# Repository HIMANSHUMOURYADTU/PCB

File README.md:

# 🔌 Transformerless Power Supply PCB (2-Layer Design)

A compact, cost-effective **transformerless AC-DC power supply** PCB, designed on a **2-layer board**, ideal for low-power embedded systems or IoT applications. This design eliminates bulky transformers using capacitive dropper topology.

---

## ⚙️ Features

- 🧩 **Transformerless AC to DC Conversion**
- 🌐 **Input Voltage**: 230V AC (mains)
- ⚡ **Output Voltage**: 12V DC (based on design)
- 🔄 **Capacitive Dropper Circuit**
- 🧯 Overvoltage and short-circuit protection
- 🖨️ **2-Layer PCB** for easy fabrication
- 🔬 Designed using **KiCad** / *(change if EasyEDA, etc.)*

---

## 📁 Project Files

| File/Folder        | Description                                  |
|--------------------|----------------------------------------------|
| `*.powerwithouttrans.kicad_prl`      | KiCad project file                           |
| `*.powerwithouttrans_pcb`            | PCB layout                                   |
| `*.kicad_sch`                        | Circuit schematic                            |
| `images/`                            | PCB renders and layout screenshots           |
| `README.md`                          | This documentation                           |
| `LICENSE`                            | Open source license (e.g., MIT or CERN-OHL)  |

---

## 🧠 Circuit Description

This power supply utilizes an **X-rated safety capacitor** to drop mains AC voltage, followed by:
- **Bridge rectifier** for AC to DC conversion
- **Zener diode** or **regulator IC** for voltage stabilization
- **Snubber network & fuse** for protection

⚠️ **Caution**: This is a **non-isolated** design and must be used with care. Do not touch the circuit while it's powered. Suitable for **low-current, enclosed applications only**.

---

## 🖼️ PCB Layout & 3D View

| Top View | Bottom View |
|----------|-------------|
|  |  |

---

---

## 📝 License

This project is licensed under the **MIT License**. See the `LICENSE` file for more information.

---

## 🤝 Contributing

Contributions are welcome! Feel free to fork this repository, make enhancements, and submit a pull request.

---

## 📬 Contact

For questions or collaboration:
- ✉️ Email: `himanshumouryaa.2004@gmail.com`
- 🌐 GitHub: [HIMANSHUMOURYADTU](https://github.com/HIMANSHUMOURYADTU)

---

> ⚠️ **Disclaimer**: This project involves direct mains voltage. Only qualified individuals should handle or modify the circuit. The creator is not responsible for any damage or injury caused by misuse.

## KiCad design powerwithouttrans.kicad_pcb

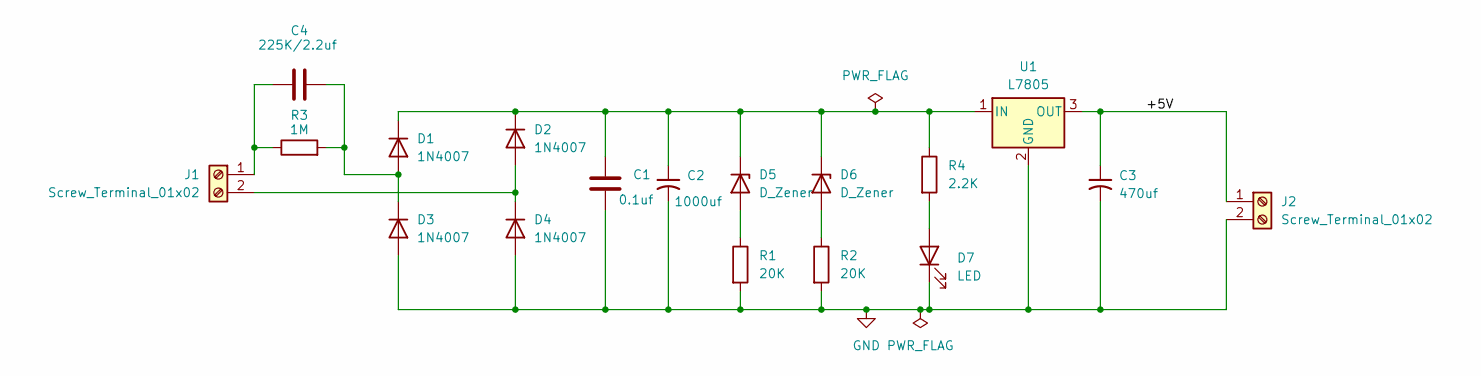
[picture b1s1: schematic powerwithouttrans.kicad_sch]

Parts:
C1: 0.1uf; C_Disc_D4.7mm_W2.5mm_P5.00mm
C2: 1000uf; CP_Radial_D10.0mm_P5.00mm
C3: 470uf; CP_Radial_D10.0mm_P3.80mm
C4: 225K/2.2uf; C_Rect_L18.0mm_W6.0mm_P15.00mm_FKS3_FKP3
D1, D2, D3, D4: 1N4007; D_DO-41_SOD81_P10.16mm_Horizontal
D5, D6: D_Zener; D_A-405_P7.62mm_Horizontal
D7: LED; LED_D5.0mm
J1, J2: Screw_Terminal_01x02; TerminalBlock_bornier-2_P5.08mm
R1, R2: 20K; R_Axial_DIN0207_L6.3mm_D2.5mm_P7.62mm_Horizontal
R3: 1M; R_Axial_DIN0207_L6.3mm_D2.5mm_P7.62mm_Horizontal
R4: 2.2K; R_Axial_DIN0207_L6.3mm_D2.5mm_P7.62mm_Horizontal
U1: L7805; TO-220-3_Vertical

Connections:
/+5V: C3.1, J2.1, U1.3 (OUT)
GND: C1.2, C2.2, C3.2, D3.2 (A), D4.2 (A), D7.1 (K), J2.2, R1.2, R2.2, U1.2 (GND)
unnamed: C4.1, D1.2 (A), D3.1 (K), R3.2
unnamed: C1.1, C2.1, D1.1 (K), D2.1 (K), D5.1 (K), D6.1 (K), R4.1, U1.1 (IN)
unnamed: D2.2 (A), D4.1 (K), J1.2
unnamed: D5.2 (A), R1.1
unnamed: D6.2 (A), R2.1
unnamed: D7.2 (A), R4.2
unnamed: C4.2, J1.1, R3.1

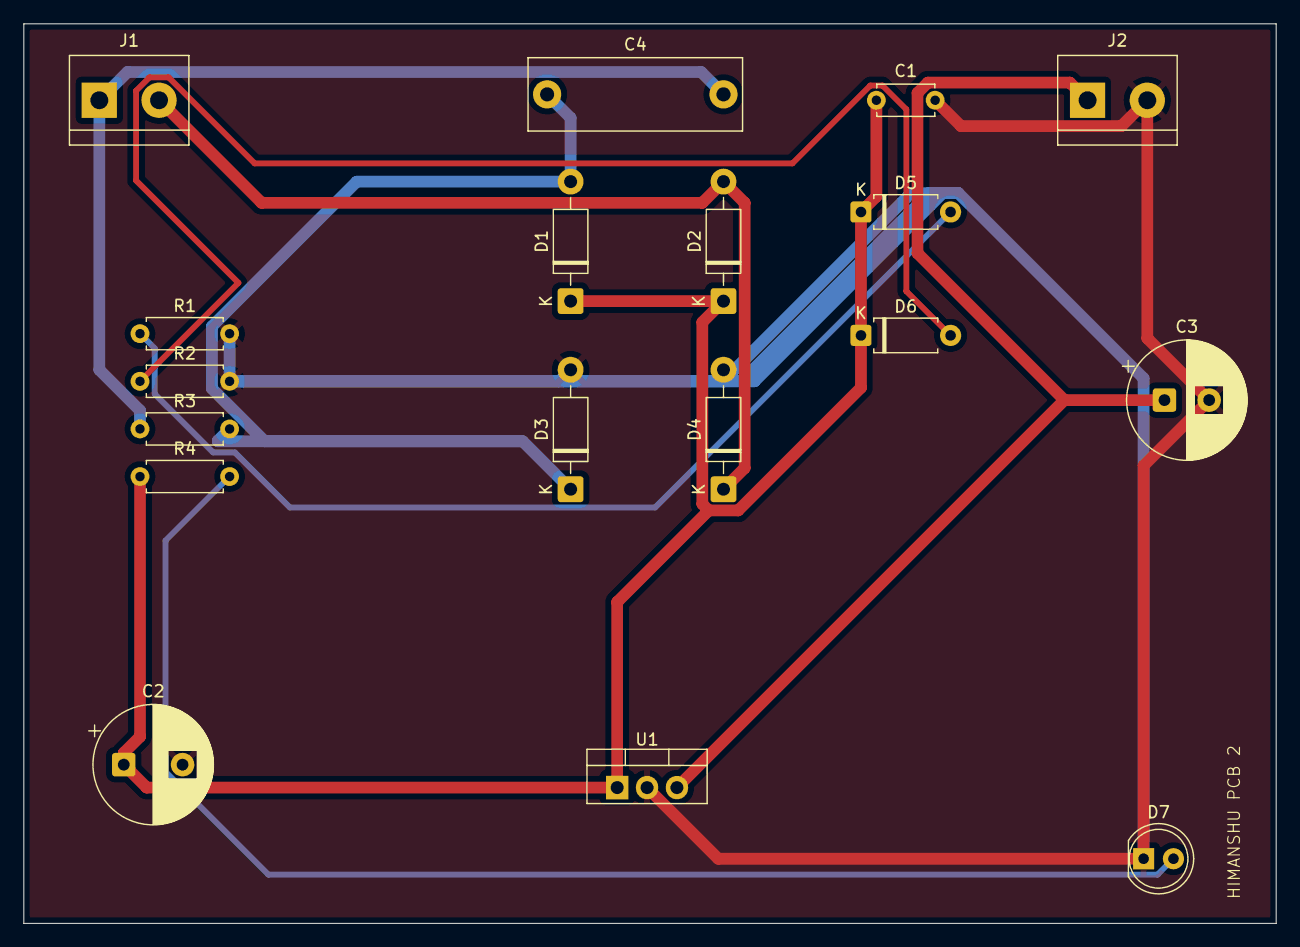
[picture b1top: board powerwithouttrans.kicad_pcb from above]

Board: 2 copper layers, 106.5 x 76.5 mm, 18 parts (0 on the bottom side), 9 nets.
